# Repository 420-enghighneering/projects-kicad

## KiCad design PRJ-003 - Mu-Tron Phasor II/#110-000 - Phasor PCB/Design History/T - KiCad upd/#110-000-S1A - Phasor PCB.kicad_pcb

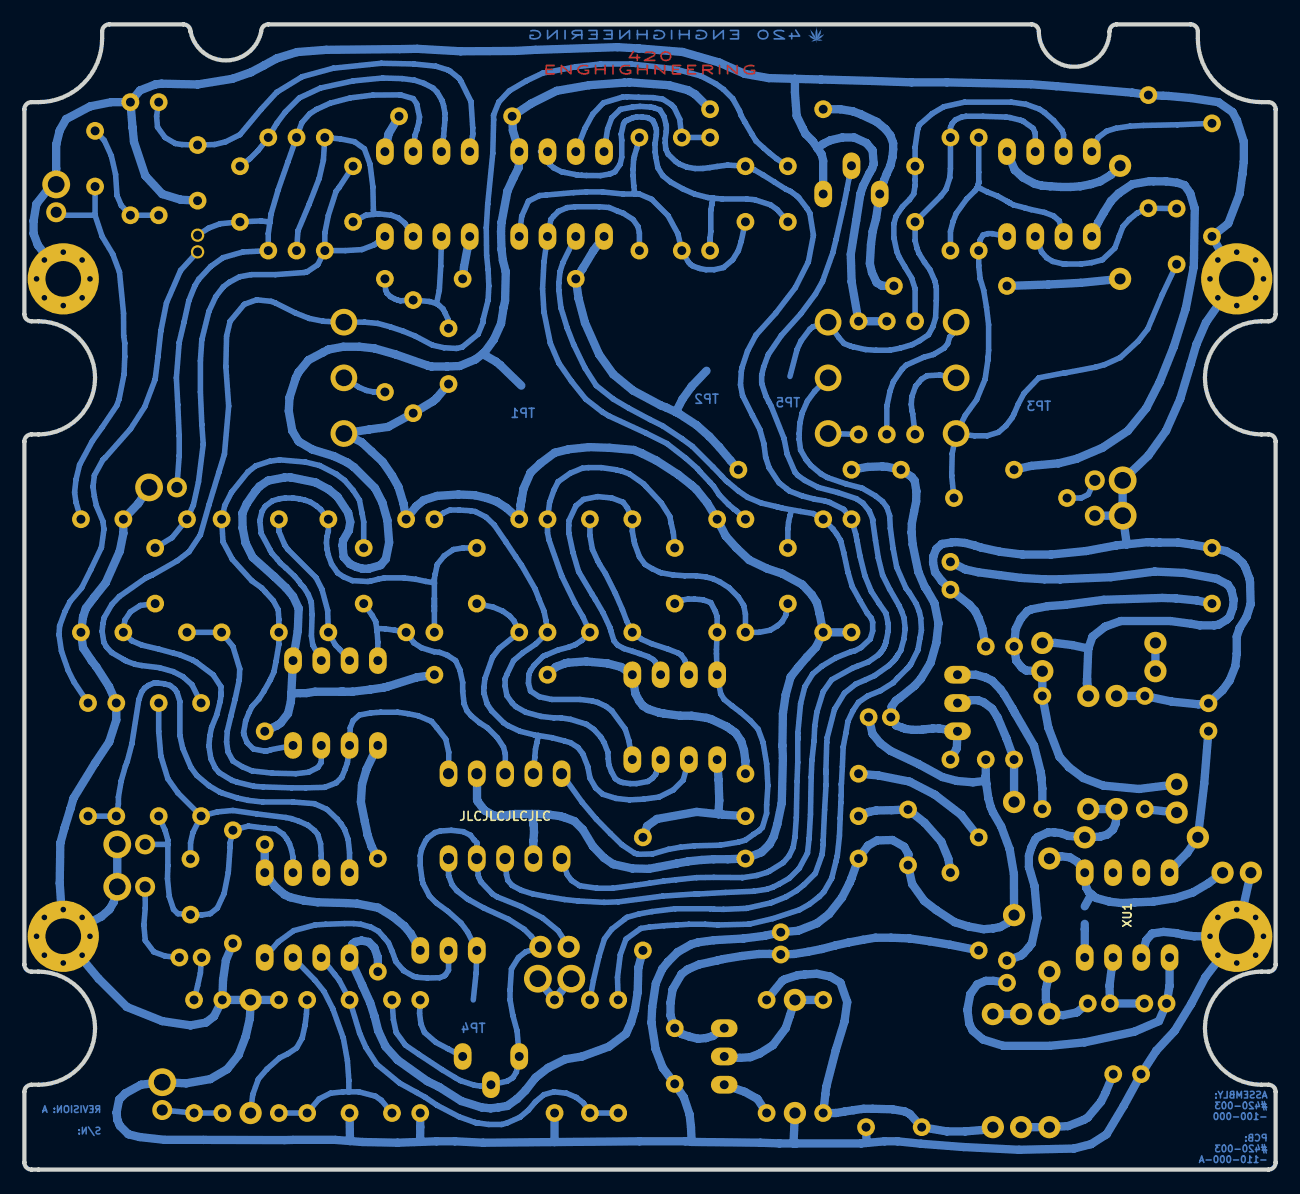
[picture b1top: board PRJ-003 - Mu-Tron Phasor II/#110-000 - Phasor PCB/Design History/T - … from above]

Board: 2 copper layers, 112.4 x 102.9 mm, 206 parts (1 on the bottom side), 76 nets.

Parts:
C1: 47n; C_MKS2F024701C00KSSD
C2: 33p; C_FKP2O100331D00JSSD
C3: 100n; C_MKS2C031001A00KSSD
C4: 1n; C_FKS2G011001A00KSSD
C5: 3n3; C_FKS2G013301A00KSSD
C6, C7, C8, C9, C10, C11, C23: 6n8; C_FKS2G016801B00KSSD
C12, C16: 470n; C_MKS2C034701C00KSSD
C13: 1u; C_UMA1H010MDD
C14: 820p; C_FKP2J008201D00HSSD
C15: 10u; C_UMA1V100MDD
D8, D9: 1N4148; D_P10.16_DO35
E0: Power Supply; E_WIRE_PAD_2x
E1: Input & Shield; E_WIRE_PAD_2x_SHIELD
E3: SW_NO; E_WIRE_PAD_2x_SHIELD
E4: SW_NC; E_WIRE_PAD_2x_SHIELD
E5: SW_COM; E_WIRE_PAD_2x_SHIELD
E6: Output & Shield; E_WIRE_PAD_2x_SHIELD
EX1: LED 1 GND; E_WIRE_PAD_2x_SHIELD_2x
EX2: LED 1 GND; E_WIRE_PAD_2x_SHIELD
G1: Logo; LOGO_36KDPI
H_A2, H_A4, H_A5, H_A6: NPTH; E_MH_PAD_M3_VIA
H_B1, H_B2, H_B3, H_B4, H_B5, H_B6, H_B7, H_B8, H_B9, H_B10, H_B11, H_B12, H_B13, H_B15, H_B16, H_B17, H_B19, H_B20, H_B21, H_B23, H_B24, H_B25, H_B26, H_B27, H_B28, H_B29, H_B30, H_B31, H_B32, H_B33, H_B34, H_B35, H_B36, H_B37, H_B38, H_B39, H_B40, H_B41, H_B42, H_B43, H_B44, H_B45, H_B46, H_B47, H_B48, H_B49, H_B50, H_B51, H_B52, H_B53, H_B54, H_B55, H_B56, H_B57, H_B58, H_B59: NPTH; E_ZIPTIE_NPTH
JP1, JP2, JP3, JP4, JP5, JP6, JP7, JP8, JP9, JP10, JP11, JP12, JP13, JP14, JP15, JP16, JP17: 0R; R_0R_JUMPER_P10.16_BCU
PM1: Photomodule; PM_DIP-10
Q1: 2N3904; Q_P2.54
R1, R3: 390k; R_P10.16
R2: 3k9; R_P10.16
R4, R5, R6, R8, R9, R11, R12, R14, R15, R17, R18, R20, R21, R23, R24: 4k7; R_P10.16
R7, R27, R29: 8k2; R_P10.16
R10, R13, R16, R19, R22, R25, R43: 220k; R_P10.16
R26, R28, R42: 10k; R_P10.16
R30, R35, R57: 27k; R_P10.16
R31, R36: 560R; R_P10.16
R32, R39: 47k; R_P10.16
R33: 56k; R_P10.16
R34: 82R; R_P10.16
R37: 82k; R_P10.16
R41: 3k3; R_P10.16
R44: 68k; R_P10.16
R45: 220R; R_P10.16
R56: 100k; R_P10.16
RV51: 10k; R_TRIM
RV52: 1k; R_TRIM
RV53, RV54: B10k; R_POT
RV55: A25k; R_POT
TP1: TP1; TP_SMD_R_3mm
TP2: TP2; TP_SMD_R_3mm
TP3: TP3; TP_SMD_R_3mm
TP4: TP4; TP_SMD_R_3mm
TP5: TP5; TP_SMD_R_3mm
XC1, XC2, XC3: 10u; C_UMA1V100MDD
XC4, XC5, XC6: 100u; C_UMA1E101MDD
XC7, XC8: 470u; C_ANGLED
XC9, XC10: 47u; C_UMA1V470MDD
XC11, XC12: 10n; C_FKS2G021001C00KSSD
XD1, XD4, XD5, XD6, XD7, XD8, XD9: 1N4001; D_P10.16
XD2, XD3: 1N5817; D_P10.16
XD10, XD11: 1N4742; D_P10.16_DO35
XJP1: Jumper_Boost; R_0603_1608M
XQ1: 2N3904; Q_P2.54
XQ2: 2N3906; Q_P2.54
XR1, XR2: 1k8; R_P10.16
XR3, XR4: 100R; R_P10.16
XR5: CLR; R_P10.16
XU1: LT1054; U_DIP-8_LT1054
YD1: LED; E_WIRE_PAD_2x_SHIELD_REVERSED
YD2: LED; E_WIRE_PAD_2x
YD3: LED_VSUPPLY; E_WIRE_PAD_2x
YR1, YR2: 1M; R_P10.16
YR3: CLR; R_P10.16
Z1, Z2, Z3, Z4, Z5, Z6: RC4558; U_DIP-8

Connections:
+9V: E0.1, XD3.1, XJP1.2, XU1.8
+12V: D8.1, JP1.1, JP1.2, JP2.1, JP2.2, JP3.1, JP3.2, JP4.1, JP4.2, JP5.1, JP5.2, JP6.1, JP6.2, JP7.1, JP7.2, Q1.3, RV51.3, TP1.1, XC9.1, XC11.1, XQ1.1, Z1.8, Z2.8, Z3.8, Z4.8, Z5.8
-12V: JP8.1, JP8.2, JP9.1, JP9.2, JP10.1, JP10.2, JP11.1, JP11.2, JP12.1, JP12.2, JP13.1, JP13.2, JP14.1, JP14.2, TP2.1, XC10.2, XC12.2, XQ2.1, Z1.4, Z2.4, Z3.4, Z4.4, Z5.4, Z6.4
GND: C2.2, C5.2, D9.2, E0.2, E1.2, E3.2, E4.2, E5.2, E6.2, EX1.1, EX1.2, EX2.1, EX2.2, H_A2.1, H_A4.1, H_A5.1, H_A6.1, JP15.1, JP15.2, JP16.1, JP16.2, JP17.1, JP17.2, PM1.4, PM1.9, R1.1, R6.2, R10.2, R13.2, R16.2, R19.2, R22.2, R25.2, R29.1, R30.1, R34.1, R36.1, R41.2, R44.1, R45.2, R56.1, R57.1, RV51.1, RV53.1, XC4.2, XC5.1, XC6.1, XC7.2, XC8.1, XC9.2, XC10.1, XC11.2, XC12.1, XD1.2, XD10.1, XD11.2, XR5.1, XU1.3, YD1.1, YR1.1, YR2.1
unnamed: C1.1, E1.1, YR1.2
unnamed: C1.2, R1.2, R2.1
unnamed: C2.1, R2.2, Z1.5
unnamed: C3.1, R3.1, Z1.6
unnamed: C4.1, R4.2, R5.1, Z1.2
unnamed: C4.2, C6.1, R5.2, R8.2, Z1.1
unnamed: C5.1, R6.1, R7.2, Z1.3
unnamed: C6.2, PM1.10, R10.1, Z2.3
unnamed: C7.1, R9.1, R11.2, Z2.1
unnamed: C7.2, PM1.8, R13.1, Z2.5
unnamed: C8.1, R12.1, R14.2, Z2.7
unnamed: C8.2, PM1.7, R16.1, Z3.3
unnamed: C9.1, R15.1, R17.2, Z3.1
unnamed: C9.2, PM1.6, R19.1, Z3.5
unnamed: C10.1, R18.1, R20.2, Z3.7
unnamed: C10.2, PM1.5, R22.1, Z4.3
unnamed: C11.1, R21.1, R23.2, Z4.1
unnamed: C11.2, PM1.3, R25.1, Z4.5
unnamed: C12.1, R24.1, Z4.7
unnamed: C12.2, R26.2, RV53.3
unnamed: C3.2, C13.1, E3.1, R3.2, R4.1, Z1.7
unnamed: C13.2, R28.2
unnamed: C14.1, R26.1, R27.2, Z5.6
unnamed: C14.2, E4.1, R27.1, R30.2, Z5.7
unnamed: C15.1, E5.1
unnamed: C15.2, R31.1
unnamed: C16.1, R35.1, Z6.6
unnamed: C16.2, R32.1, RV54.3, TP5.1, Z6.7
unnamed: C23.1, R56.2, Z6.2
unnamed: C23.2, R33.1, RV55.3, TP3.1, YR3.2, Z6.1
unnamed: D8.2, Z6.8
unnamed: D9.1, R42.1
unnamed: E6.1, R31.2, YR2.2
unnamed: PM1.1, R43.1, RV52.1, RV52.2, YD2.1
unnamed: PM1.2, Q1.1, TP4.1, YD2.2
unnamed: Q1.2, Z5.1
unnamed: R7.1, RV53.2
unnamed: R8.1, R9.2, Z2.2
unnamed: R11.1, R12.2, Z2.6
unnamed: R14.1, R15.2, Z3.2
unnamed: R17.1, R18.2, Z3.6
unnamed: R20.1, R21.2, Z4.2
unnamed: R23.1, R24.2, Z4.6
unnamed: R28.1, R29.2, Z5.5
unnamed: R32.2, R33.2, Z6.3
unnamed: R34.2, RV55.1
unnamed: R35.2, RV55.2
unnamed: R36.2, RV54.1
unnamed: R37.1, RV54.2
unnamed: R37.2, R39.2, R41.1, Z5.3
unnamed: R39.1, RV51.2
unnamed: R42.2, R43.2, R44.2, Z5.2
unnamed: R45.1, RV52.3
unnamed: R57.2, Z6.5
unnamed: XC1.1, XD2.1, XD3.2
unnamed: XC1.2, XC2.1, XU1.2
unnamed: XC2.2, XC3.1, XU1.4
unnamed: XC3.2, XD1.1, XD4.1, XD5.2
unnamed: XC4.1, XD2.2, XD6.1
unnamed: XC5.2, XD4.2, XU1.5
unnamed: XC6.2, XD5.1, XD8.2
unnamed: XC7.1, XD7.2, XR1.1, XR3.2
unnamed: XC8.2, XD9.1, XR2.2, XR4.2, YD3.1
unnamed: XD6.2, XD7.1
unnamed: XD8.1, XD9.2
unnamed: XD10.2, XQ1.2, XR1.2
unnamed: XD11.1, XQ2.2, XR2.1
unnamed: XJP1.1, XU1.1
unnamed: XQ1.3, XR3.1
unnamed: XQ2.3, XR4.1
unnamed: XR5.2, YD3.2
unnamed: YD1.2, YR3.1

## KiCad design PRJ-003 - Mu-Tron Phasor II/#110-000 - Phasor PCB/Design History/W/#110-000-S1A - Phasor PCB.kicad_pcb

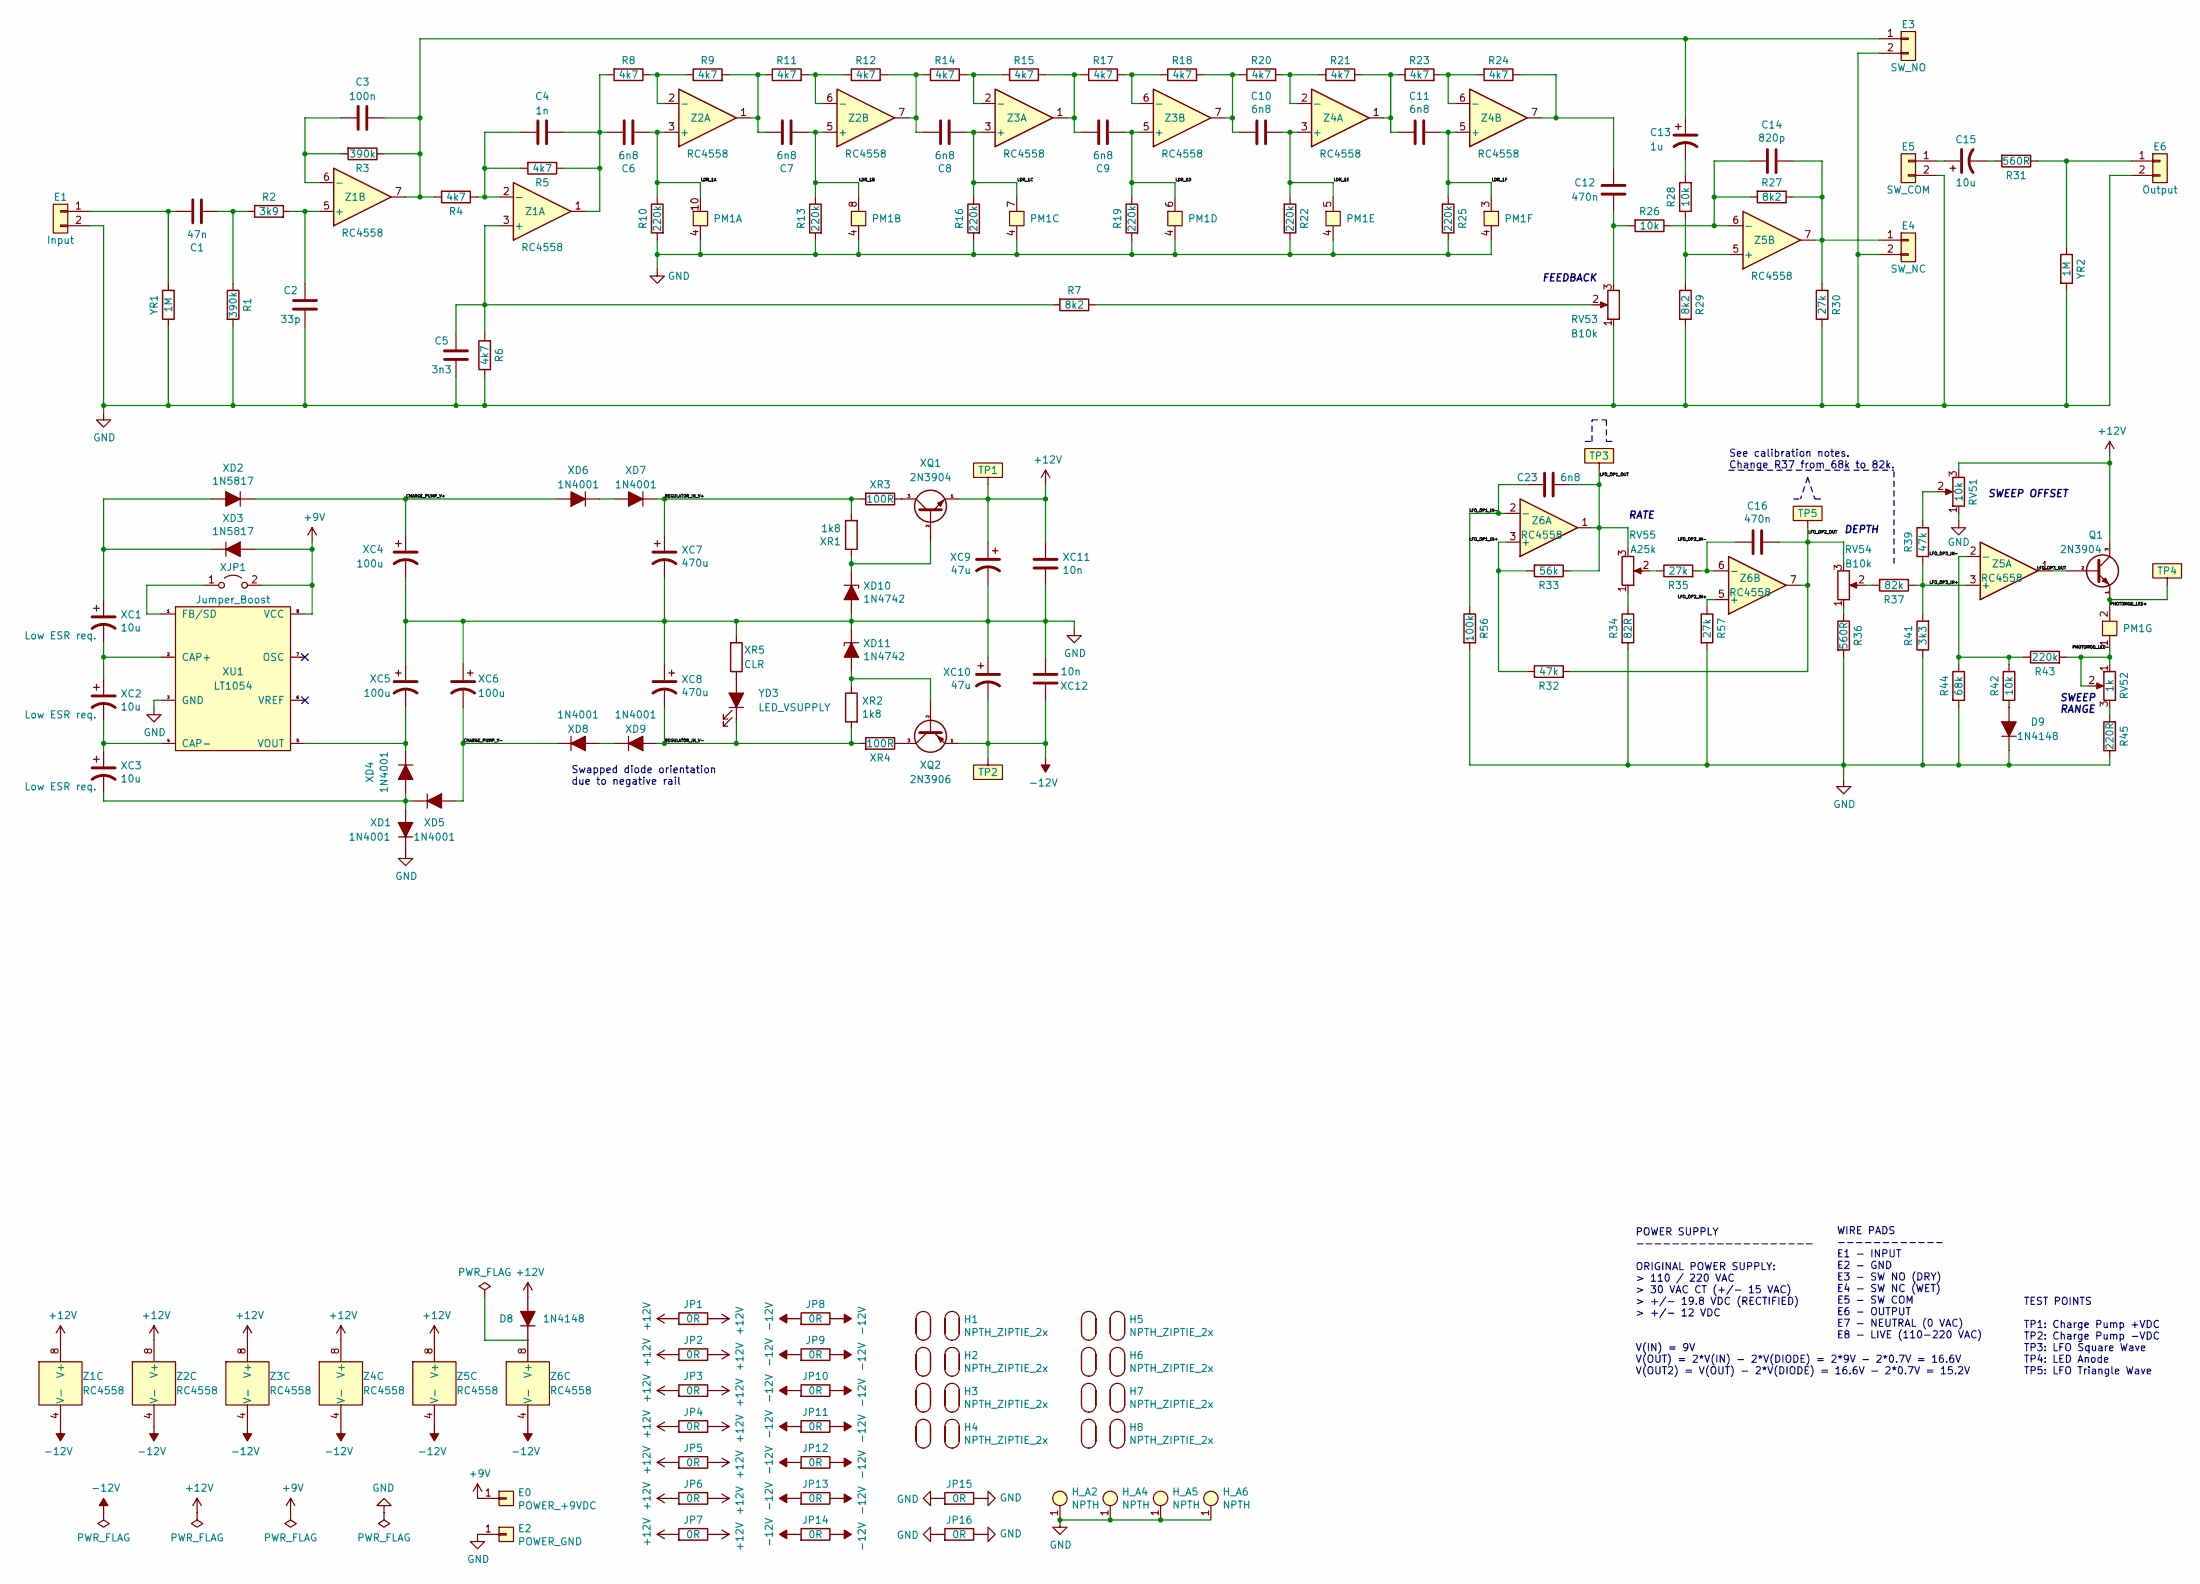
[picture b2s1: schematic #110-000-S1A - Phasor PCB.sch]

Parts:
C1: 47n; C_MKS2F024701C00KSSD
C2: 33p; C_FKP2O100331D00JSSD
C3: 100n; C_MKS2C031001A00KSSD
C4: 1n; C_FKS2G011001A00KSSD
C5: 3n3; C_FKS2G013301A00KSSD
C6, C7, C8, C9, C10, C11, C23: 6n8; C_FKS2G016801B00KSSD
C12, C16: 470n; C_MKS2C034701C00KSSD
C13: 1u; C_UMA1H010MDD
C14: 820p; C_FKP2J008201D00HSSD
C15: 10u; C_UMA1V100MDD
D8, D9: 1N4148; D_P10.16_DO35
E0: POWER_+9VDC; E_WIRE_PAD_1x_ZIPTIE_NPTH_2x
E1: Input; E_WIRE_PAD_1x_SHIELD_PAD_1x_ZIPTIE_NPTH_2x
E2: POWER_GND; E_WIRE_PAD_1x_ZIPTIE_NPTH_2x
E3: SW_NO; E_WIRE_PAD_1x_SHIELD_PAD_1x_ZIPTIE_NPTH_2x
E4: SW_NC; E_WIRE_PAD_1x_SHIELD_PAD_1x_ZIPTIE_NPTH_2x
E5: SW_COM; E_WIRE_PAD_1x_SHIELD_PAD_1x_ZIPTIE_NPTH_2x
E6: Output; E_WIRE_PAD_1x_SHIELD_PAD_1x_ZIPTIE_NPTH_2x
H1, H2, H3, H4, H5, H6, H7, H8: NPTH_ZIPTIE_2x; E_ZIPTIE_NPTH_2x_P2.54mm
H_A2, H_A4, H_A5, H_A6: NPTH; E_MH_PAD_M3_VIA_HEXSPACER
JP1, JP2, JP3, JP4, JP5, JP6, JP7, JP8, JP9, JP10, JP11, JP12, JP13, JP14, JP15, JP16: 0R; R_0R_JUMPER_P10.16
PM1: Photomodule; PM_DIP-10
Q1: 2N3904; Q_P2.54
R1, R3: 390k; R_CF_P10.16_390k
R2: 3k9; R_CF_P10.16_3k9
R4, R5, R6, R8, R9, R11, R12, R14, R15, R17, R18, R20, R21, R23, R24: 4k7; R_CF_P10.16_4k7
R7, R27, R29: 8k2; R_CF_P10.16_8k2
R10, R13, R16, R19, R22, R25, R43: 220k; R_CF_P10.16_220k
R26, R28, R42: 10k; R_CF_P10.16_10k
R30, R35, R57: 27k; R_CF_P10.16_27k
R31, R36: 560R; R_CF_P10.16_560R
R32, R39: 47k; R_CF_P10.16_47k
R33: 56k; R_CF_P10.16_56k
R34: 82R; R_CF_P10.16_82R
R37: 82k; R_CF_P10.16_82k
R41: 3k3; R_CF_P10.16_3k3
R44: 68k; R_CF_P10.16_68k
R45: 220R; R_CF_P10.16_220R
R56: 100k; R_CF_P10.16_100k
RV51: 10k; R_TRIM
RV52: 1k; R_TRIM
RV53, RV54: B10k; R_POT
RV55: A25k; R_POT
TP1: TP1; TP_SMD_R_3mm
TP2: TP2; TP_SMD_R_3mm
TP3: TP3; TP_SMD_R_3mm
TP4, TP5: TP5; TP_SMD_R_3mm
XC1, XC2, XC3: 10u; C_UMA1V100MDD
XC4, XC5, XC6: 100u; C_UMA1E101MDD
XC7, XC8: 470u; C_ANGLED
XC9, XC10: 47u; C_UMA1V470MDD
XC11, XC12: 10n; C_FKS2G021001C00KSSD
XD1, XD4, XD5, XD6, XD7, XD8, XD9: 1N4001; D_P10.16
XD2, XD3: 1N5817; D_P10.16
XD10, XD11: 1N4742; D_P10.16_DO35
XJP1: Jumper_Boost; R_0603_1608M
XQ1: 2N3904; Q_P2.54
XQ2: 2N3906; Q_P2.54
XR1, XR2: 1k8; R_CF_P10.16_1k8
XR3, XR4: 100R; R_CF_P10.16_100R
XR5: CLR; R_CF_P10.16_2k2
XU1: LT1054; U_DIP-8_LT1054
YD3: LED_VSUPPLY; E_WIRE_PAD_2x_ZIPTIE_NPTH_2x_CIRC
YR1, YR2: 1M; R_CF_P10.16_1M
Z1, Z2, Z3, Z4, Z5, Z6: RC4558; U_DIP-8

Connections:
+9V: E0.1, XD3.1 (A), XJP1.2 (B), XU1.8 (VCC)
+12V: D8.1 (A), JP1.1, JP1.2, JP2.1, JP2.2, JP3.1, JP3.2, JP4.1, JP4.2, JP5.1, JP5.2, JP6.1, JP6.2, JP7.1, JP7.2, Q1.3 (C), RV51.3, TP1.1, XC9.1, XC11.1, XQ1.1 (E), Z1.8 (V+), Z2.8 (V+), Z3.8 (V+), Z4.8 (V+), Z5.8 (V+)
-12V: JP8.1, JP8.2, JP9.1, JP9.2, JP10.1, JP10.2, JP11.1, JP11.2, JP12.1, JP12.2, JP13.1, JP13.2, JP14.1, JP14.2, TP2.1, XC10.2, XC12.1, XQ2.1 (E), Z1.4 (V-), Z2.4 (V-), Z3.4 (V-), Z4.4 (V-), Z5.4 (V-), Z6.4 (V-)
/CHARGE_PUMP_V+: XC4.1, XD2.2 (K), XD6.1 (A)
/CHARGE_PUMP_V-: XC6.2, XD5.1 (A), XD8.2 (K)
/LDR_1A: C6.2, PM1.10, R10.1, Z2.3 (+)
/LDR_1B: C7.2, PM1.8, R13.1, Z2.5 (+)
/LDR_1C: C8.2, PM1.7, R16.1, Z3.3 (+)
/LDR_1D: C9.2, PM1.6, R19.1, Z3.5 (+)
/LDR_1E: C10.1, PM1.5, R22.2, Z4.3 (+)
/LDR_1F: C11.1, PM1.3, R25.2, Z4.5 (+)
/LFO_OP1_IN+: R32.1, R33.2, Z6.3 (+)
/LFO_OP1_IN-: C23.1, R56.1, Z6.2 (-)
/LFO_OP1_OUT: C23.2, R33.1, RV55.3, TP3.1, Z6.1
/LFO_OP2_IN+: R57.1, Z6.5 (+)
/LFO_OP2_IN-: C16.1, R35.2, Z6.6 (-)
/LFO_OP2_OUT: C16.2, R32.2, RV54.3, TP5.1, Z6.7
/LFO_OP3_OUT: Q1.2 (B), Z5.1
/PHOTOMOD_LED+: PM1.2, Q1.1 (E), TP4.1
/PHOTOMOD_LED-: PM1.1, R43.2, RV52.1, RV52.2
/REGULATOR_IN_V+: XC7.1, XD7.2 (K), XR1.2, XR3.2
/REGULATOR_IN_V-: XC8.2, XD9.1 (A), XR2.2, XR4.2, YD3.1 (K)
GND: C2.2, C5.2, D9.2 (K), E1.2, E2.1, E3.2, E4.2, E5.2, E6.2, H_A2.1, H_A4.1, H_A5.1, H_A6.1, JP15.1, JP15.2, JP16.1, JP16.2, PM1.4, PM1.9, R1.2, R6.1, R10.2, R13.2, R16.2, R19.2, R22.1, R25.1, R29.2, R30.1, R34.2, R36.2, R41.1, R44.2, R45.1, R56.2, R57.2, RV51.1, RV53.1, XC4.2, XC5.1, XC6.1, XC7.2, XC8.1, XC9.2, XC10.1, XC11.2, XC12.2, XD1.2 (K), XD10.1 (A), XD11.2 (K), XR5.2, XU1.3 (GND), YR1.1, YR2.2
unnamed: C1.1, R1.1, R2.1
unnamed: C1.2, E1.1, YR1.2
unnamed: C2.1, R2.2, Z1.5 (+)
unnamed: C3.2, R3.2, Z1.6 (-)
unnamed: C4.1, C6.1, R5.1, R8.2, Z1.1
unnamed: C4.2, R4.1, R5.2, Z1.2 (-)
unnamed: C5.1, R6.2, R7.2, Z1.3 (+)
unnamed: C7.1, R9.2, R11.1, Z2.1
unnamed: C8.1, R12.2, R14.1, Z2.7
unnamed: C9.1, R15.2, R17.1, Z3.1
unnamed: C10.2, R18.2, R20.1, Z3.7
unnamed: C11.2, R21.2, R23.1, Z4.1
unnamed: C12.1, R24.1, Z4.7
unnamed: C12.2, R26.2, RV53.3
unnamed: C3.1, C13.1, E3.1, R3.1, R4.2, Z1.7
unnamed: C13.2, R28.2
unnamed: C14.1, R26.1, R27.2, Z5.6 (-)
unnamed: C14.2, E4.1, R27.1, R30.2, Z5.7
unnamed: C15.1, E5.1
unnamed: C15.2, R31.2
unnamed: D8.2 (K), Z6.8 (V+)
unnamed: D9.1 (A), R42.2
unnamed: E6.1, R31.1, YR2.1
unnamed: R7.1, RV53.2
unnamed: R8.1, R9.1, Z2.2 (-)
unnamed: R11.2, R12.1, Z2.6 (-)
unnamed: R14.2, R15.1, Z3.2 (-)
unnamed: R17.2, R18.1, Z3.6 (-)
unnamed: R20.2, R21.1, Z4.2 (-)
unnamed: R23.2, R24.2, Z4.6 (-)
unnamed: R28.1, R29.1, Z5.5 (+)
unnamed: R34.1, RV55.1
unnamed: R35.1, RV55.2
unnamed: R36.1, RV54.1
unnamed: R37.2, RV54.2
unnamed: R39.2, RV51.2
unnamed: R45.2, RV52.3
unnamed: XC1.1, XD2.1 (A), XD3.2 (K)
unnamed: XC1.2, XC2.1, XU1.2 (CAP+)
unnamed: XC2.2, XC3.1, XU1.4 (CAP-)
unnamed: XC3.2, XD1.1 (A), XD4.1 (A), XD5.2 (K)
unnamed: XC5.2, XD4.2 (K), XU1.5 (VOUT)
unnamed: XD6.2 (K), XD7.1 (A)
unnamed: XD8.1 (A), XD9.2 (K)
unnamed: XD10.2 (K), XQ1.2 (B), XR1.1
unnamed: XD11.1 (A), XQ2.2 (B), XR2.1
unnamed: XJP1.1 (A), XU1.1 (FB/SD)
unnamed: XQ1.3 (C), XR3.1
unnamed: XQ2.3 (C), XR4.1
unnamed: XR5.1, YD3.2 (A)

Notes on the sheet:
FEEDBACK
See calibration notes. Change R37 from 68k to 82k.
SWEEP OFFSET
DEPTH
TEST POINTS TP1: Charge Pump +VDC TP2: Charge Pump -VDC TP3: LFO Square Wave TP4: LED Anode TP5: LFO Triangle Wave
POWER SUPPLY -------------------- ORIGINAL POWER SUPPLY: > 110 / 220 VAC > 30 VAC CT (+/- 15 VAC) > +/- 19.8 VDC (RECTIFIED) > +/- 12 VDC V(IN) = 9V V(OUT) = 2*V(IN) - 2*V(DIODE) = 2*9V - 2*0.7V = 16.6V V(OUT2) = V(OUT) - 2*V(DIODE) = 16.6V - 2*0.7V = 15.2V
WIRE PADS ------------ E1 - INPUT E2 - GND E3 - SW NO (DRY) E4 - SW NC (WET) E5 - SW COM E6 - OUTPUT E7 - NEUTRAL (0 VAC) E8 - LIVE (110-220 VAC)
SWEEP RANGE
RATE
Swapped diode orientation due to negative rail

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
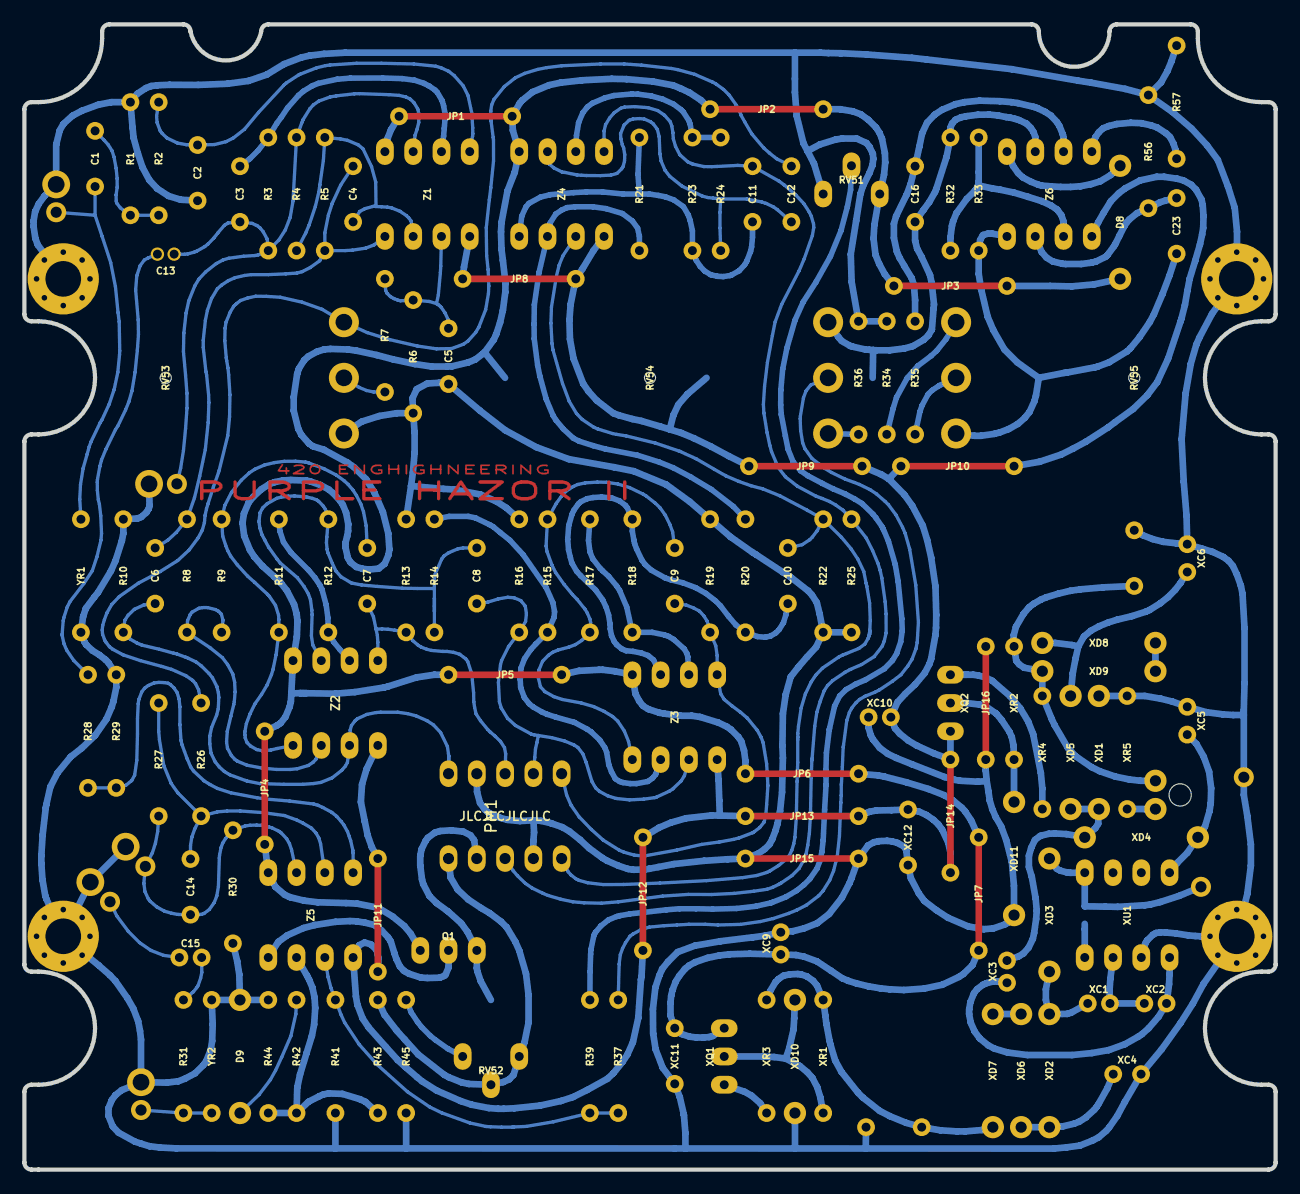
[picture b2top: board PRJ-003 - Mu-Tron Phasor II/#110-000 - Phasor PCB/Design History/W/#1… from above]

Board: 2 copper layers, 112.4 x 102.9 mm, 152 parts (1 on the bottom side), 75 nets.

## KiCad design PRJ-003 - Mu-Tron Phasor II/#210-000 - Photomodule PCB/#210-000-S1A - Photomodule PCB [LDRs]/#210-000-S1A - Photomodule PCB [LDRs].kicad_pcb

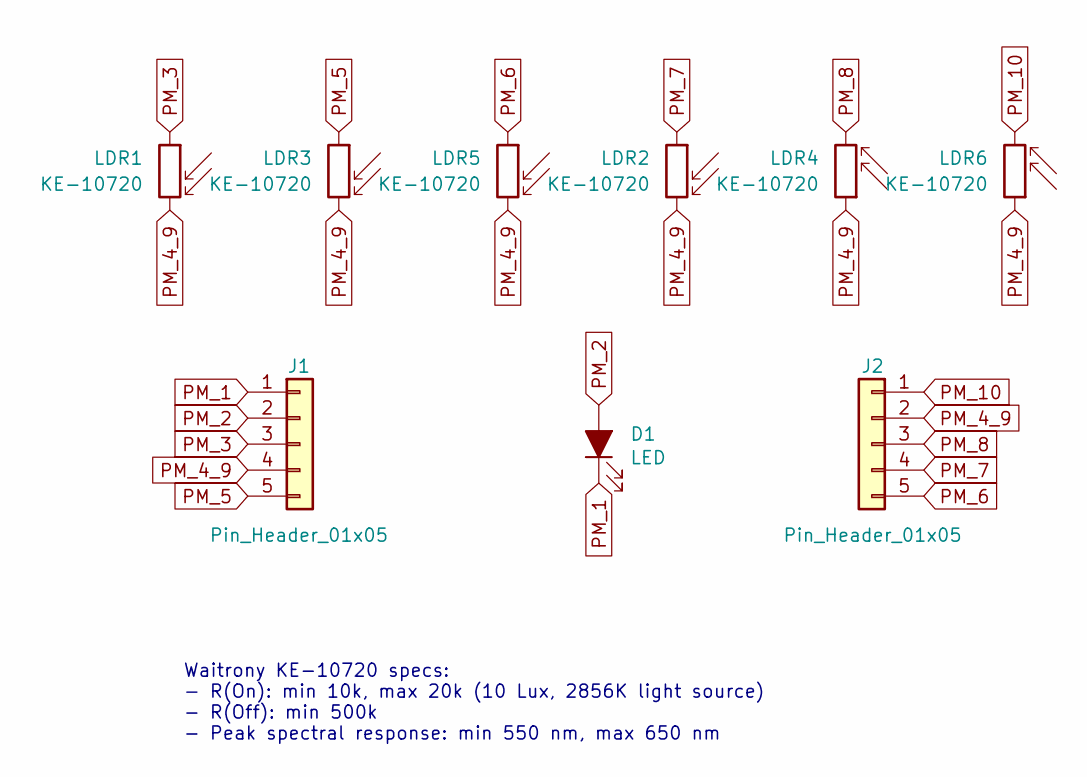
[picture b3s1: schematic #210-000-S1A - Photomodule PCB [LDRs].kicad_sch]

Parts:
D1: LED; D_LED
J1, J2: Pin_Header_01x05; E_HEADER_1x05_P2.54_SMALLERPADS
LDR1, LDR2, LDR3, LDR4, LDR5, LDR6: KE-10720; R_LDR_SMALLERPAD

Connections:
PM_1: D1.1 (K), J1.1
PM_2: D1.2 (A), J1.2
PM_3: J1.3, LDR1.1
PM_4_9: J1.4, J2.2, LDR1.2, LDR2.2, LDR3.2, LDR4.1, LDR5.2, LDR6.1
PM_5: J1.5, LDR3.1
PM_6: J2.5, LDR5.1
PM_7: J2.4, LDR2.1
PM_8: J2.3, LDR4.2
PM_10: J2.1, LDR6.2

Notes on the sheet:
Waitrony KE-10720 specs: - R(On): min 10k, max 20k (10 Lux, 2856K light source) - R(Off): min 500k - Peak spectral response: min 550 nm, max 650 nm

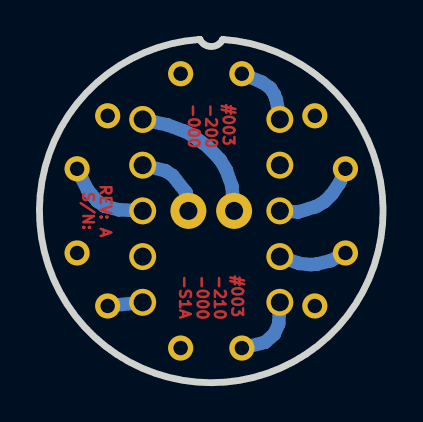
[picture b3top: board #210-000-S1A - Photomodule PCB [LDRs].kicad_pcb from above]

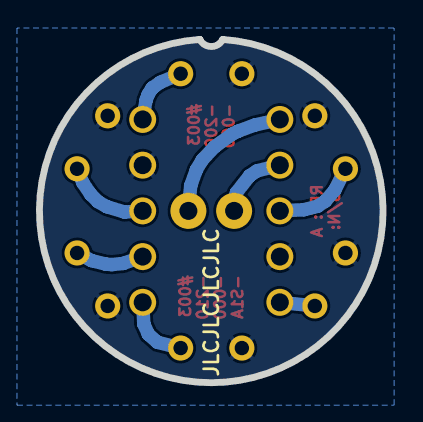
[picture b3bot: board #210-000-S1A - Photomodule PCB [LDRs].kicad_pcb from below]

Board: 2 copper layers, 19.1 x 19.1 mm, 9 parts (2 on the bottom side), 9 nets.

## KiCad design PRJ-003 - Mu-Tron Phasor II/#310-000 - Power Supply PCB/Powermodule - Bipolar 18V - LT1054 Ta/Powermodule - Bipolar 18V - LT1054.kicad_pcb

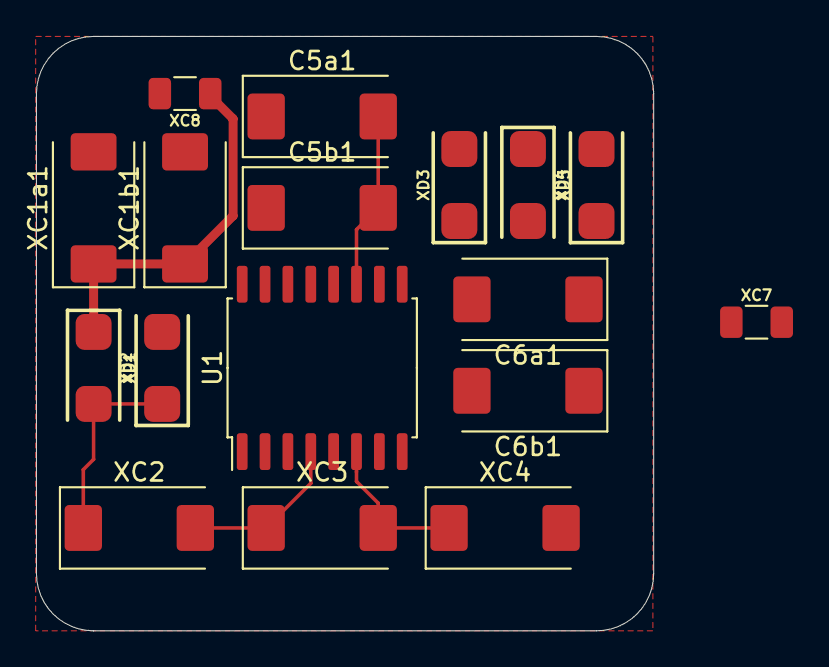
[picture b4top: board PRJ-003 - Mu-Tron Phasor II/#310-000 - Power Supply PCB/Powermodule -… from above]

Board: 2 copper layers, 34.3 x 33.0 mm, 17 parts (0 on the bottom side), 9 nets.

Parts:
C5a1, C5b1, C6a1, C6b1: 47u; AVX_TAJ_EIA_2917_7343-43M_Case_E_47u_35V
U1: LT1054IDW
XC1a1, XC1b1: 47u; AVX_TAJ_EIA_2917_7343-43M_Case_E_47u_35V
XC2, XC3, XC4: 10u; AVX_TAJ_EIA_2917_7343-20M_Case_Y_10u_35V
XC7, XC8: 100n; C_1206_3216M_h1.00
XD1, XD2, XD3, XD4, XD5: 1N5817; Rectron_FM5817-W

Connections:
+9V: U1.14, XD2.1
GND: C5a1.1, C5b1.1, C6a1.1, C6b1.1, U1.5, XC1a1.2, XC1b1.2, XC7.2, XC8.2, XD4.2
unnamed: C5a1.2, C5b1.2, U1.11, XD3.2
unnamed: U1.4, XC2.2, XC3.1
unnamed: U1.6, XC3.2, XC4.1
unnamed: XC2.1, XD1.1, XD2.2
unnamed: XC4.2, XD3.1, XD4.1, XD5.2
VCC: XC1a1.1, XC1b1.1, XC8.1, XD1.2
VSS: C6a1.2, C6b1.2, XC7.1, XD5.1

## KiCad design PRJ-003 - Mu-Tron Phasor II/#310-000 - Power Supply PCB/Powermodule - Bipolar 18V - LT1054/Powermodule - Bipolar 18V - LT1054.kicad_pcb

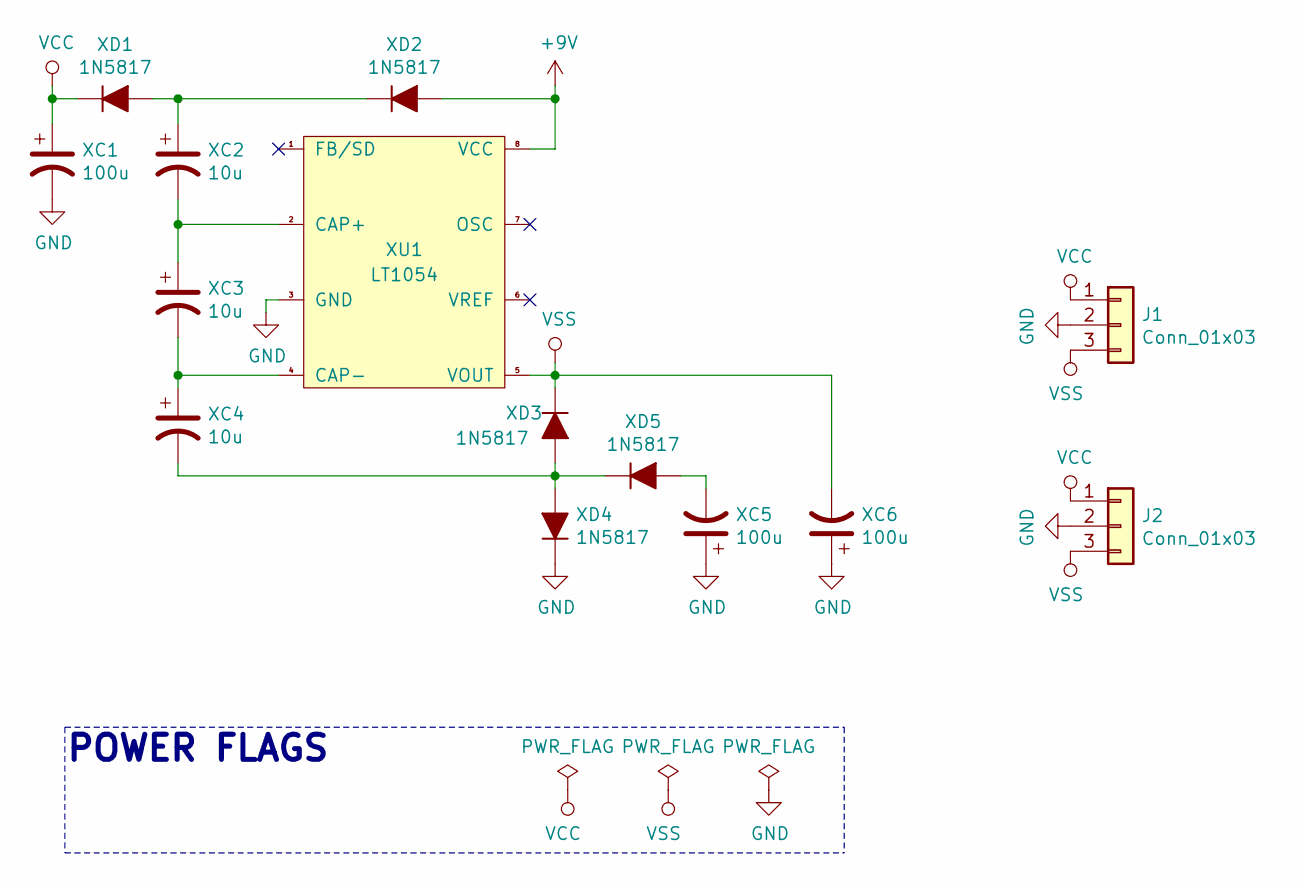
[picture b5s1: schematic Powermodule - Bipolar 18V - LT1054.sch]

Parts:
J1, J2: Conn_01x03; PinHeader_1x03_P2.54mm_Vertical_Top
XC1, XC5, XC6: 100u; Nichicon_UMA1E101MDD_100uF_P2.50_8.0x5.0mm
XC2, XC3, XC4: 10u; Nichicon_UMA1E100MDD_10uF_P2.00_5.0x5.0mm
XD1, XD2, XD3, XD4, XD5: 1N5817; DO-41_P10.16
XU1: LT1054

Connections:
+9V: XD2.1 (A), XU1.8 (VCC)
GND: J1.2, J2.2, XC1.2, XC5.1, XC6.1, XD4.2 (K), XU1.3 (GND)
unnamed: XC2.1, XD1.1 (A), XD2.2 (K)
unnamed: XC2.2, XC3.1, XU1.2 (CAP+)
unnamed: XC3.2, XC4.1, XU1.4 (CAP-)
unnamed: XC4.2, XD3.1 (A), XD4.1 (A), XD5.2 (K)
unnamed: XC5.2, XD5.1 (A)
VCC: J1.1, J2.1, XC1.1, XD1.2 (K)
VSS: J1.3, J2.3, XC6.2, XD3.2 (K), XU1.5 (VOUT)

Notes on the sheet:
POWER FLAGS

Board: 2 copper layers, 14 parts (2 on the bottom side), 9 nets, no tracks yet.
